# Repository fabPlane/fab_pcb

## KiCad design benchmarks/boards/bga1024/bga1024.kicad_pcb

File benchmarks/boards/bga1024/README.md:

# Eight-layer 1,024-net candidate and report-limit control

Original MIT synthetic fixture, seed 6512. Requires native `pcbnew`, `kicad-cli`
10.0.6 and an output directory that does not exist:

```sh
/usr/bin/python3 -O benchmarks/boards/bga1024/generate.py /tmp/bga1024-new --seed 6512
bun run typecheck
/usr/bin/python3 -O benchmarks/boards/bga1024/test_generate.py
FAB_ROUTER_MODULE=$HOME/bench/repos/fab_router/src/api.ts bun run test:unit
```

The 90 × 90 mm board has eight signal copper layers, a 32 × 32 BGA at 0.5 mm
pitch with 0.2 mm round pads, and four 4 × 64 destination banks with 0.4 mm pads,
0.8 mm horizontal pitch and 1.5 mm row pitch. Each of 1,024 nets has exactly two
terminals (2,048 pads total); destinations are shuffled by the recorded seed.
Track/clearance are 0.10/0.10 mm; through-via diameter/drill are 0.30/0.10 mm.
The companion project is required. There are no planes, pair constraints,
length groups or external footprint libraries. This is an unrouted candidate;
input admission establishes neither routed feasibility nor relative difficulty.

The generator reloads the board and checks net ownership, copper layers,
effective project rules, no tracks/zones, and a fresh native DRC with zero
geometry violations. It exports DSN with a stable root filename. The board,
project and DSN reproduce byte for byte across output directories.

## Native report limit discovered by this board

Native connectivity reports **1,024 opens**, while the fresh DRC JSON report
contains **499 unconnected findings**. These are distinct observations, both
recorded in `summary.json`. KiCad 10.0.6 caps unconnected and clearance findings
at 499 and most other types at 199 in
[its DRC engine](https://github.com/KiCad/kicad-source-mirror/blob/10.0.6/pcbnew/drc/drc_engine.cpp).
A report at the boundary cannot prove an exact count: 499 observed findings
may represent 499 or more actual opens. The fixture remains a diagnostic candidate.
The generator intentionally admits this known report-limited control; it does
not substitute the report count for native connectivity or publish completion.

The benchmark contribution rejects reports at or above the per-type thresholds
before native quality publication and changes cache identity. It conservatively
rejects exact-boundary reports too. Reports below the thresholds are not thereby
proven complete; ignored checks and checker/dependency policy remain separate.
Production native baseline adoption remains pending. The frozen benchmark is
unchanged.

This public contribution contains only the original board, deterministic generator,
native admission test and measurement evidence outside the frozen suite. It does
not change any production router, native checker, scoring or ranked cache policy.
The report-limit rejection was measured in the separate benchmark harness.

Report admission also requires the expected report schema and board name, a
nonempty checker version, error/warning/exclusion coverage, all finding lists,
empty schematic parity and correctly typed error opens. Missing or inconsistent
evidence cannot support the generator's zero-violation diagnostic. Three paired
controls preserve valid admission3/3 while reducing acceptance of nine malformed
variants27/27 to0/27. The mutations apply to fresh reports, not native boards.

```sh
nice -n 10 taskset -c 0-5 timeout 120 /usr/bin/python3 -O benchmarks/boards/bga1024/test_report.py --measure /tmp/bga1024-admission-controls
```

Use a new output directory. The full evidence and limits are retained under
`docs/pr-assets/agent/bga1024-candidate/`.

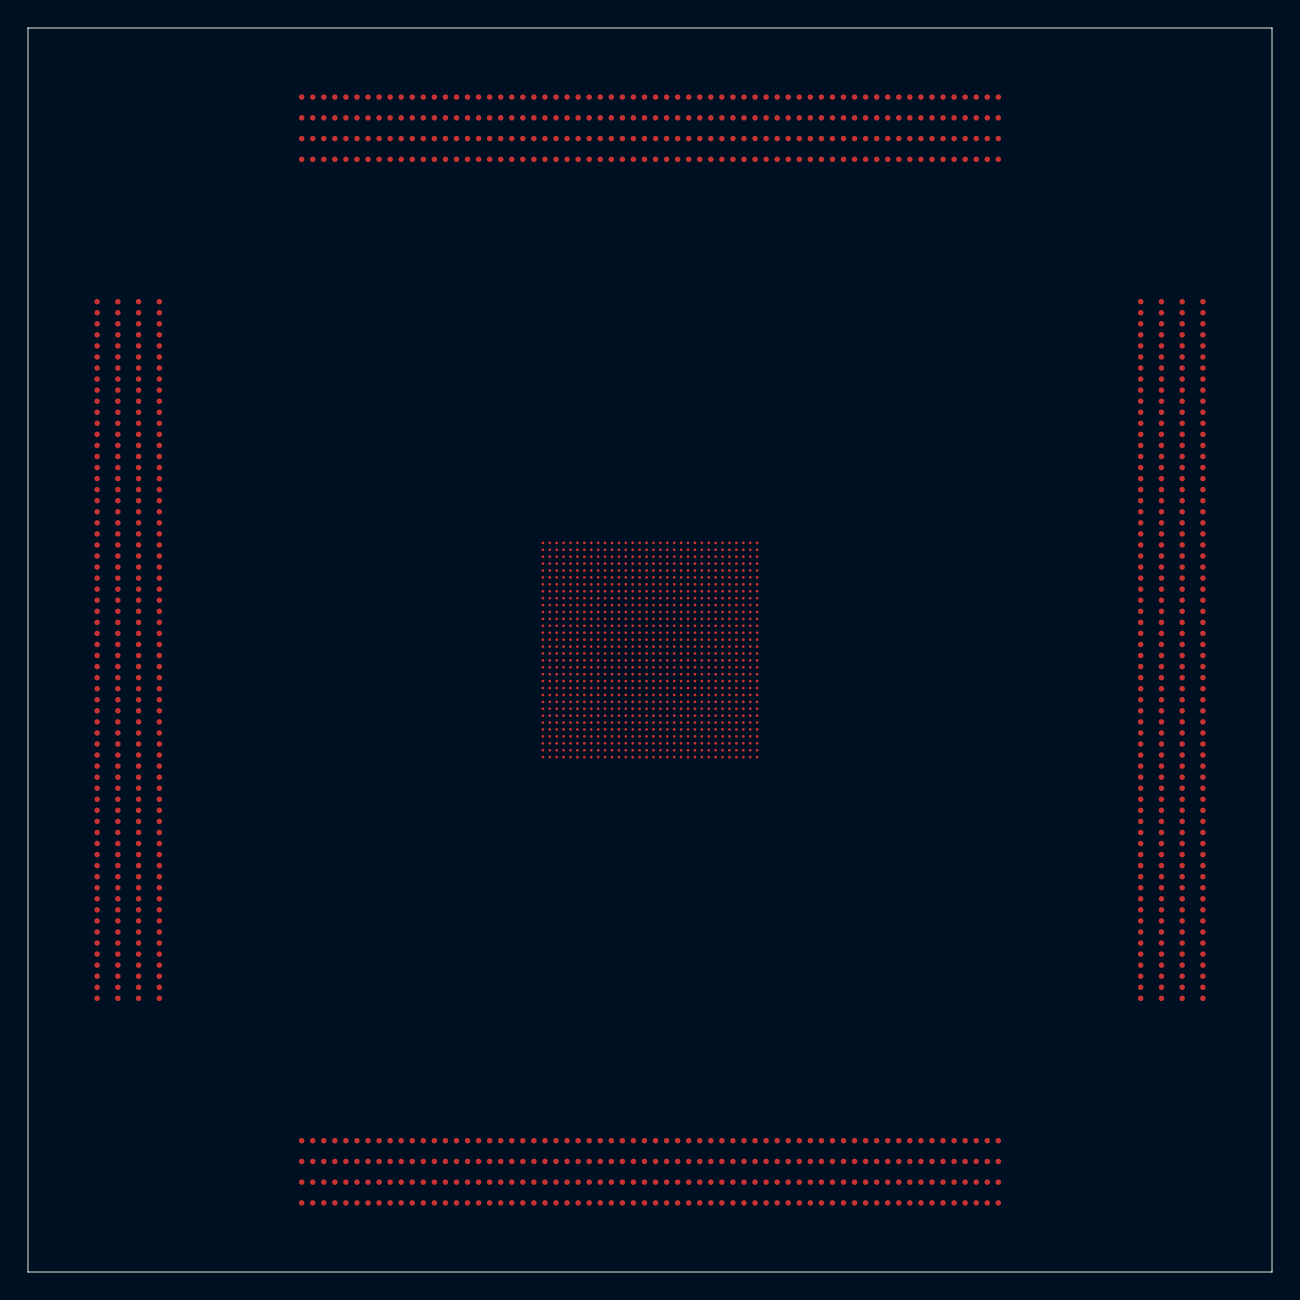
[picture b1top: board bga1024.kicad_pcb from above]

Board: 8 copper layers, 90.0 x 90.0 mm, 1025 parts (0 on the bottom side), 1024 nets, no tracks yet.

Parts:
J1, J2, J3, J4, J5, J6, J7, J8, J9, J10, J11, J12, J13, J14, J15, J16, J17, J18, J19, J20, J21, J22, J23, J24, J25, J26, J27, J28, J29, J30, J31, J32, J33, J34, J35, J36, J37, J38, J39, J40, J41, J42, J43, J44, J45, J46, J47, J48, J49, J50, J51, J52, J53, J54, J55, J56, J57, J58, J59, J60, J61, J62, J63, J64, J65, J66, J67, J68, J69, J70, J71, J72, J73, J74, J75, J76, J77, J78, J79, J80, J81, J82, J83, J84, J85, J86, J87, J88, J89, J90, J91, J92, J93, J94, J95, J96, J97, J98, J99, J100, J101, J102, J103, J104, J105, J106, J107, J108, J109, J110, J111, J112, J113, J114, J115, J116, J117, J118, J119, J120, J121, J122, J123, J124, J125, J126, J127, J128, J129, J130, J131, J132, J133, J134, J135, J136, J137, J138, J139, J140, J141, J142, J143, J144, J145, J146, J147, J148, J149, J150, J151, J152, J153, J154, J155, J156, J157, J158, J159, J160, J161, J162, J163, J164, J165, J166, J167, J168, J169, J170, J171, J172, J173, J174, J175, J176, J177, J178, J179, J180, J181, J182, J183, J184, J185, J186, J187, J188, J189, J190, J191, J192, J193, J194, J195, J196, J197, J198, J199, J200, J201, J202, J203, J204, J205, J206, J207, J208, J209, J210, J211, J212, J213, J214, J215, J216, J217, J218, J219, J220, J221, J222, J223, J224, J225, J226, J227, J228, J229, J230, J231, J232, J233, J234, J235, J236, J237, J238, J239, J240, J241, J242, J243, J244, J245, J246, J247, J248, J249, J250, J251, J252, J253, J254, J255, J256, J257, J258, J259, J260, J261, J262, J263, J264, J265, J266, J267, J268, J269, J270, J271, J272, J273, J274, J275, J276, J277, J278, J279, J280, J281, J282, J283, J284, J285, J286, J287, J288, J289, J290, J291, J292, J293, J294, J295, J296, J297, J298, J299, J300, J301, J302, J303, J304, J305, J306, J307, J308, J309, J310, J311, J312, J313, J314, J315, J316, J317, J318, J319, J320, J321, J322, J323, J324, J325, J326, J327, J328, J329, J330, J331, J332, J333, J334, J335, J336, J337, J338, J339, J340, J341, J342, J343, J344, J345, J346, J347, J348, J349, J350, J351, J352, J353, J354, J355, J356, J357, J358, J359, J360, J361, J362, J363, J364, J365, J366, J367, J368, J369, J370, J371, J372, J373, J374, J375, J376, J377, J378, J379, J380, J381, J382, J383, J384, J385, J386, J387, J388, J389, J390, J391, J392, J393, J394, J395, J396, J397, J398, J399, J400, J401, J402, J403, J404, J405, J406, J407, J408, J409, J410, J411, J412, J413, J414, J415, J416, J417, J418, J419, J420, J421, J422, J423, J424, J425, J426, J427, J428, J429, J430, J431, J432, J433, J434, J435, J436, J437, J438, J439, J440, J441, J442, J443, J444, J445, J446, J447, J448, J449, J450, J451, J452, J453, J454, J455, J456, J457, J458, J459, J460, J461, J462, J463, J464, J465, J466, J467, J468, J469, J470, J471, J472, J473, J474, J475, J476, J477, J478, J479, J480, J481, J482, J483, J484, J485, J486, J487, J488, J489, J490, J491, J492, J493, J494, J495, J496, J497, J498, J499, J500, J501, J502, J503, J504, J505, J506, J507, J508, J509, J510, J511, J512, J513, J514, J515, J516, J517, J518, J519, J520, J521, J522, J523, J524, J525, J526, J527, J528, J529, J530, J531, J532, J533, J534, J535, J536, J537, J538, J539, J540, J541, J542, J543, J544, J545, J546, J547, J548, J549, J550, J551, J552, J553, J554, J555, J556, J557, J558, J559, J560, J561, J562, J563, J564, J565, J566, J567, J568, J569, J570, J571, J572, J573, J574, J575, J576, J577, J578, J579, J580, J581, J582, J583, J584, J585, J586, J587, J588, J589, J590, J591, J592, J593, J594, J595, J596, J597, J598, J599, J600, J601, J602, J603, J604, J605, J606, J607, J608, J609, J610, J611, J612, J613, J614, J615, J616, J617, J618, J619, J620, J621, J622, J623, J624, J625, J626, J627, J628, J629, J630, J631, J632, J633, J634, J635, J636, J637, J638, J639, J640, J641, J642, J643, J644, J645, J646, J647, J648, J649, J650, J651, J652, J653, J654, J655, J656, J657, J658, J659, J660, J661, J662, J663, J664, J665, J666, J667, J668, J669, J670, J671, J672, J673, J674, J675, J676, J677, J678, J679, J680, J681, J682, J683, J684, J685, J686, J687, J688, J689, J690, J691, J692, J693, J694, J695, J696, J697, J698, J699, J700, J701, J702, J703, J704, J705, J706, J707, J708, J709, J710, J711, J712, J713, J714, J715, J716, J717, J718, J719, J720, J721, J722, J723, J724, J725, J726, J727, J728, J729, J730, J731, J732, J733, J734, J735, J736, J737, J738, J739, J740, J741, J742, J743, J744, J745, J746, J747, J748, J749, J750, J751, J752, J753, J754, J755, J756, J757, J758, J759, J760, J761, J762, J763, J764, J765, J766, J767, J768, J769, J770, J771, J772, J773, J774, J775, J776, J777, J778, J779, J780, J781, J782, J783, J784, J785, J786, J787, J788, J789, J790, J791, J792, J793, J794, J795, J796, J797, J798, J799, J800, J801, J802, J803, J804, J805, J806, J807, J808, J809, J810, J811, J812, J813, J814, J815, J816, J817, J818, J819, J820, J821, J822, J823, J824, J825, J826, J827, J828, J829, J830, J831, J832, J833, J834, J835, J836, J837, J838, J839, J840, J841, J842, J843, J844, J845, J846, J847, J848, J849, J850, J851, J852, J853, J854, J855, J856, J857, J858, J859, J860, J861, J862, J863, J864, J865, J866, J867, J868, J869, J870, J871, J872, J873, J874, J875, J876, J877, J878, J879, J880, J881, J882, J883, J884, J885, J886, J887, J888, J889, J890, J891, J892, J893, J894, J895, J896, J897, J898, J899, J900, J901, J902, J903, J904, J905, J906, J907, J908, J909, J910, J911, J912, J913, J914, J915, J916, J917, J918, J919, J920, J921, J922, J923, J924, J925, J926, J927, J928, J929, J930, J931, J932, J933, J934, J935, J936, J937, J938, J939, J940, J941, J942, J943, J944, J945, J946, J947, J948, J949, J950, J951, J952, J953, J954, J955, J956, J957, J958, J959, J960, J961, J962, J963, J964, J965, J966, J967, J968, J969, J970, J971, J972, J973, J974, J975, J976, J977, J978, J979, J980, J981, J982, J983, J984, J985, J986, J987, J988, J989, J990, J991, J992, J993, J994, J995, J996, J997, J998, J999, J1000, J1001, J1002, J1003, J1004, J1005, J1006, J1007, J1008, J1009, J1010, J1011, J1012, J1013, J1014, J1015, J1016, J1017, J1018, J1019, J1020, J1021, J1022, J1023, J1024: escape
U1: escape

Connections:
N1: J358.1, U1.1
N2: J174.2, U1.2
N3: J613.3, U1.3
N4: J73.4, U1.4
N5: J63.5, U1.5
N6: J190.6, U1.6
N7: J628.7, U1.7
N8: J419.8, U1.8
N9: J303.9, U1.9
N10: J916.10, U1.10
N11: J950.11, U1.11
N12: J748.12, U1.12
N13: J988.13, U1.13
N14: J910.14, U1.14
N15: J129.15, U1.15
N16: J452.16, U1.16
N17: J112.17, U1.17
N18: J65.18, U1.18
N19: J379.19, U1.19
N20: J351.20, U1.20
N21: J818.21, U1.21
N22: J10.22, U1.22
N23: J605.23, U1.23
N24: J975.24, U1.24
N25: J929.25, U1.25
N26: J697.26, U1.26
N27: J151.27, U1.27
N28: J108.28, U1.28
N29: J467.29, U1.29
N30: J881.30, U1.30
N31: J1017.31, U1.31
N32: J602.32, U1.32
N33: J445.33, U1.33
N34: J212.34, U1.34
N35: J489.35, U1.35
N36: J476.36, U1.36
N37: J655.37, U1.37
N38: J618.38, U1.38
N39: J856.39, U1.39
N40: J32.40, U1.40
N41: J69.41, U1.41
N42: J763.42, U1.42
N43: J198.43, U1.43
N44: J940.44, U1.44
N45: J255.45, U1.45
N46: J302.46, U1.46
N47: J273.47, U1.47
N48: J540.48, U1.48
N49: J196.49, U1.49
N50: J229.50, U1.50
N51: J576.51, U1.51
N52: J819.52, U1.52
N53: J966.53, U1.53
N54: J4.54, U1.54
N55: J70.55, U1.55
N56: J524.56, U1.56
N57: J363.57, U1.57
N58: J672.58, U1.58
N59: J858.59, U1.59
N60: J963.60, U1.60
N61: J987.61, U1.61
N62: J410.62, U1.62
N63: J327.63, U1.63
N64: J638.64, U1.64
N65: J121.65, U1.65
N66: J991.66, U1.66
N67: J415.67, U1.67
N68: J864.68, U1.68
N69: J435.69, U1.69
N70: J593.70, U1.70
N71: J236.71, U1.71
N72: J660.72, U1.72
N73: J825.73, U1.73
N74: J683.74, U1.74
N75: J74.75, U1.75
N76: J465.76, U1.76
N77: J253.77, U1.77
N78: J38.78, U1.78
N79: J943.79, U1.79
N80: J741.80, U1.80
N81: J501.81, U1.81
N82: J475.82, U1.82
N83: J53.83, U1.83
N84: J592.84, U1.84
N85: J578.85, U1.85
N86: J885.86, U1.86
N87: J869.87, U1.87
N88: J999.88, U1.88
N89: J932.89, U1.89
N90: J295.90, U1.90
N91: J842.91, U1.91
N92: J539.92, U1.92
N93: J333.93, U1.93
N94: J360.94, U1.94
N95: J876.95, U1.95
N96: J348.96, U1.96
N97: J50.97, U1.97
N98: J454.98, U1.98
N99: J846.99, U1.99
N100: J119.100, U1.100
N101: J231.101, U1.101
N102: J67.102, U1.102
N103: J706.103, U1.103
N104: J297.104, U1.104
N105: J554.105, U1.105
N106: J611.106, U1.106
N107: J380.107, U1.107
N108: J541.108, U1.108
N109: J791.109, U1.109
N110: J972.110, U1.110
N111: J39.111, U1.111
N112: J998.112, U1.112
N113: J582.113, U1.113
N114: J753.114, U1.114
N115: J786.115, U1.115
N116: J1016.116, U1.116
N117: J596.117, U1.117
N118: J673.118, U1.118
N119: J532.119, U1.119
N120: J982.120, U1.120
N121: J788.121, U1.121
N122: J874.122, U1.122
N123: J90.123, U1.123
N124: J100.124, U1.124
N125: J948.125, U1.125
N126: J598.126, U1.126
N127: J790.127, U1.127
N128: J136.128, U1.128
N129: J187.129, U1.129
N130: J990.130, U1.130
N131: J644.131, U1.131
N132: J424.132, U1.132
N133: J733.133, U1.133
N134: J77.134, U1.134
N135: J94.135, U1.135
N136: J433.136, U1.136
N137: J848.137, U1.137
N138: J634.138, U1.138
N139: J322.139, U1.139
N140: J1004.140, U1.140
N141: J696.141, U1.141
N142: J588.142, U1.142
N143: J191.143, U1.143
N144: J533.144, U1.144
N145: J543.145, U1.145
N146: J438.146, U1.146
N147: J931.147, U1.147
N148: J239.148, U1.148
N149: J35.149, U1.149
N150: J140.150, U1.150
N151: J870.151, U1.151
N152: J758.152, U1.152
N153: J716.153, U1.153
N154: J1020.154, U1.154
N155: J14.155, U1.155
N156: J835.156, U1.156
N157: J530.157, U1.157
N158: J714.158, U1.158
N159: J985.159, U1.159
N160: J555.160, U1.160
N161: J252.161, U1.161
N162: J793.162, U1.162
N163: J528.163, U1.163
N164: J902.164, U1.164
N165: J738.165, U1.165
N166: J556.166, U1.166
N167: J12.167, U1.167
N168: J369.168, U1.168
N169: J335.169, U1.169
N170: J723.170, U1.170
N171: J690.171, U1.171
N172: J359.172, U1.172
N173: J933.173, U1.173
N174: J305.174, U1.174
N175: J138.175, U1.175
N176: J91.176, U1.176
N177: J175.177, U1.177
N178: J907.178, U1.178
N179: J959.179, U1.179
N180: J549.180, U1.180
N181: J347.181, U1.181
N182: J650.182, U1.182
N183: J310.183, U1.183
N184: J980.184, U1.184
N185: J337.185, U1.185
N186: J219.186, U1.186
N187: J324.187, U1.187
N188: J830.188, U1.188
N189: J765.189, U1.189
N190: J389.190, U1.190
N191: J158.191, U1.191
N192: J234.192, U1.192
N193: J957.193, U1.193
N194: J183.194, U1.194
N195: J155.195, U1.195
N196: J71.196, U1.196
N197: J340.197, U1.197
N198: J285.198, U1.198
N199: J904.199, U1.199
N200: J361.200, U1.200
N201: J671.201, U1.201
N202: J574.202, U1.202
N203: J425.203, U1.203
N204: J715.204, U1.204
N205: J905.205, U1.205
N206: J882.206, U1.206
N207: J72.207, U1.207
N208: J332.208, U1.208
N209: J865.209, U1.209
N210: J908.210, U1.210
N211: J46.211, U1.211
N212: J831.212, U1.212
N213: J325.213, U1.213
N214: J166.214, U1.214
N215: J274.215, U1.215
N216: J407.216, U1.216
N217: J152.217, U1.217
N218: J98.218, U1.218
N219: J544.219, U1.219
N220: J186.220, U1.220
N221: J371.221, U1.221
N222: J460.222, U1.222
N223: J464.223, U1.223
N224: J709.224, U1.224
N225: J339.225, U1.225
N226: J1008.226, U1.226
N227: J62.227, U1.227
N228: J401.228, U1.228
N229: J208.229, U1.229
N230: J180.230, U1.230
N231: J214.231, U1.231
N232: J37.232, U1.232
N233: J996.233, U1.233
N234: J757.234, U1.234
N235: J523.235, U1.235
N236: J779.236, U1.236
N237: J260.237, U1.237
N238: J406.238, U1.238
N239: J935.239, U1.239
N240: J522.240, U1.240
N241: J545.241, U1.241
N242: J286.242, U1.242
N243: J659.243, U1.243
N244: J428.244, U1.244
N245: J58.245, U1.245
N246: J851.246, U1.246
N247: J111.247, U1.247
N248: J936.248, U1.248
N249: J85.249, U1.249
N250: J572.250, U1.250
N251: J761.251, U1.251
N252: J575.252, U1.252
N253: J877.253, U1.253
N254: J562.254, U1.254
N255: J47.255, U1.255
N256: J416.256, U1.256
N257: J206.257, U1.257
N258: J408.258, U1.258
N259: J784.259, U1.259
N260: J150.260, U1.260
N261: J623.261, U1.261
N262: J665.262, U1.262
N263: J711.263, U1.263
N264: J685.264, U1.264
N265: J747.265, U1.265
N266: J43.266, U1.266
N267: J159.267, U1.267
N268: J168.268, U1.268
N269: J639.269, U1.269
N270: J177.270, U1.270
N271: J455.271, U1.271
N272: J233.272, U1.272
N273: J680.273, U1.273
N274: J1009.274, U1.274
N275: J703.275, U1.275
N276: J726.276, U1.276
N277: J749.277, U1.277
N278: J24.278, U1.278
N279: J147.279, U1.279
N280: J204.280, U1.280
N281: J750.281, U1.281
N282: J759.282, U1.282
N283: J355.283, U1.283
N284: J531.284, U1.284
N285: J99.285, U1.285
N286: J1022.286, U1.286
N287: J293.287, U1.287
N288: J281.288, U1.288
N289: J478.289, U1.289
N290: J6.290, U1.290
N291: J441.291, U1.291
N292: J131.292, U1.292
N293: J806.293, U1.293
N294: J319.294, U1.294
N295: J1001.295, U1.295
N296: J713.296, U1.296
N297: J157.297, U1.297
N298: J828.298, U1.298
N299: J341.299, U1.299
N300: J372.300, U1.300
N301: J974.301, U1.301
N302: J511.302, U1.302
N303: J61.303, U1.303
N304: J668.304, U1.304
N305: J27.305, U1.305
N306: J64.306, U1.306
N307: J25.307, U1.307
N308: J20.308, U1.308
N309: J649.309, U1.309
N310: J632.310, U1.310
N311: J95.311, U1.311
N312: J550.312, U1.312
N313: J210.313, U1.313
N314: J947.314, U1.314
N315: J960.315, U1.315
N316: J508.316, U1.316
N317: J440.317, U1.317
N318: J647.318, U1.318
N319: J859.319, U1.319
N320: J813.320, U1.320
N321: J658.321, U1.321
N322: J956.322, U1.322
N323: J352.323, U1.323
N324: J493.324, U1.324
N325: J312.325, U1.325
N326: J51.326, U1.326
N327: J279.327, U1.327
N328: J1003.328, U1.328
N329: J586.329, U1.329
N330: J80.330, U1.330
N331: J497.331, U1.331
N332: J227.332, U1.332
N333: J635.333, U1.333
N334: J654.334, U1.334
N335: J857.335, U1.335
N336: J725.336, U1.336
N337: J901.337, U1.337
N338: J992.338, U1.338
N339: J132.339, U1.339
N340: J466.340, U1.340
N341: J667.341, U1.341
N342: J383.342, U1.342
N343: J430.343, U1.343
N344: J938.344, U1.344
N345: J590.345, U1.345
N346: J381.346, U1.346
N347: J704.347, U1.347
N348: J619.348, U1.348
N349: J486.349, U1.349
N350: J200.350, U1.350
N351: J906.351, U1.351
N352: J79.352, U1.352
N353: J814.353, U1.353
N354: J986.354, U1.354
N355: J448.355, U1.355
N356: J648.356, U1.356
N357: J924.357, U1.357
N358: J762.358, U1.358
N359: J59.359, U1.359
N360: J782.360, U1.360
N361: J93.361, U1.361
N362: J669.362, U1.362
N363: J984.363, U1.363
N364: J269.364, U1.364
N365: J280.365, U1.365
N366: J606.366, U1.366
N367: J900.367, U1.367
N368: J767.368, U1.368
N369: J349.369, U1.369
N370: J785.370, U1.370
N371: J595.371, U1.371
N372: J861.372, U1.372
N373: J583.373, U1.373
N374: J146.374, U1.374
N375: J42.375, U1.375
N376: J1023.376, U1.376
N377: J397.377, U1.377
N378: J559.378, U1.378
N379: J393.379, U1.379
N380: J894.380, U1.380
N381: J783.381, U1.381
N382: J125.382, U1.382
N383: J258.383, U1.383
N384: J429.384, U1.384
N385: J128.385, U1.385
N386: J847.386, U1.386
N387: J215.387, U1.387
N388: J925.388, U1.388
N389: J336.389, U1.389
N390: J500.390, U1.390
N391: J866.391, U1.391
N392: J627.392, U1.392
N393: J873.393, U1.393
N394: J693.394, U1.394
N395: J249.395, U1.395
N396: J496.396, U1.396
N397: J21.397, U1.397
N398: J254.398, U1.398
N399: J326.399, U1.399
N400: J370.400, U1.400
N401: J720.401, U1.401
N402: J211.402, U1.402
N403: J871.403, U1.403
N404: J390.404, U1.404
N405: J422.405, U1.405
N406: J971.406, U1.406
N407: J66.407, U1.407
N408: J220.408, U1.408
N409: J55.409, U1.409
N410: J625.410, U1.410
N411: J778.411, U1.411
N412: J843.412, U1.412
N413: J421.413, U1.413
N414: J291.414, U1.414
N415: J563.415, U1.415
N416: J184.416, U1.416
N417: J617.417, U1.417
N418: J259.418, U1.418
N419: J756.419, U1.419
N420: J232.420, U1.420
N421: J472.421, U1.421
N422: J821.422, U1.422
N423: J624.423, U1.423
N424: J450.424, U1.424
N425: J107.425, U1.425
N426: J197.426, U1.426
N427: J373.427, U1.427
N428: J11.428, U1.428
N429: J506.429, U1.429
N430: J375.430, U1.430
N431: J844.431, U1.431
N432: J535.432, U1.432
N433: J849.433, U1.433
N434: J994.434, U1.434
N435: J491.435, U1.435
N436: J637.436, U1.436
N437: J9.437, U1.437
N438: J178.438, U1.438
N439: J288.439, U1.439
N440: J643.440, U1.440
N441: J542.441, U1.441
N442: J695.442, U1.442
N443: J626.443, U1.443
N444: J742.444, U1.444
N445: J228.445, U1.445
N446: J176.446, U1.446
N447: J616.447, U1.447
N448: J527.448, U1.448
N449: J420.449, U1.449
N450: J773.450, U1.450
N451: J707.451, U1.451
N452: J275.452, U1.452
N453: J414.453, U1.453
N454: J736.454, U1.454
N455: J193.455, U1.455
N456: J705.456, U1.456
N457: J534.457, U1.457
N458: J328.458, U1.458
N459: J942.459, U1.459
N460: J28.460, U1.460
N461: J808.461, U1.461
N462: J250.462, U1.462
N463: J840.463, U1.463
N464: J983.464, U1.464
N465: J892.465, U1.465
N466: J201.466, U1.466
N467: J509.467, U1.467
N468: J36.468, U1.468
N469: J399.469, U1.469
N470: J529.470, U1.470
N471: J453.471, U1.471
N472: J964.472, U1.472
N473: J525.473, U1.473
N474: J954.474, U1.474
N475: J581.475, U1.475
N476: J899.476, U1.476
N477: J679.477, U1.477
N478: J13.478, U1.478
N479: J313.479, U1.479
N480: J518.480, U1.480
N481: J173.481, U1.481
N482: J257.482, U1.482
N483: J447.483, U1.483
N484: J515.484, U1.484
N485: J776.485, U1.485
N486: J97.486, U1.486
N487: J294.487, U1.487
N488: J512.488, U1.488
N489: J630.489, U1.489
N490: J855.490, U1.490
N491: J600.491, U1.491
N492: J833.492, U1.492
N493: J558.493, U1.493
N494: J811.494, U1.494
N495: J872.495, U1.495
N496: J521.496, U1.496
N497: J365.497, U1.497
N498: J296.498, U1.498
N499: J1.499, U1.499
N500: J225.500, U1.500
N501: J677.501, U1.501
N502: J473.502, U1.502
N503: J96.503, U1.503
N504: J678.504, U1.504
N505: J270.505, U1.505
N506: J124.506, U1.506
N507: J737.507, U1.507
N508: J978.508, U1.508
N509: J735.509, U1.509
N510: J795.510, U1.510
N511: J84.511, U1.511
N512: J724.512, U1.512
N513: J426.513, U1.513
N514: J243.514, U1.514
N515: J56.515, U1.515
N516: J34.516, U1.516
N517: J548.517, U1.517
N518: J344.518, U1.518
N519: J394.519, U1.519
N520: J276.520, U1.520
N521: J503.521, U1.521
N522: J391.522, U1.522
N523: J867.523, U1.523
N524: J287.524, U1.524
N525: J652.525, U1.525
N526: J824.526, U1.526
N527: J342.527, U1.527
N528: J87.528, U1.528
N529: J86.529, U1.529
N530: J1013.530, U1.530
N531: J182.531, U1.531
N532: J516.532, U1.532
N533: J955.533, U1.533
N534: J941.534, U1.534
N535: J567.535, U1.535
N536: J78.536, U1.536
N537: J752.537, U1.537
N538: J356.538, U1.538
N539: J1002.539, U1.539
N540: J977.540, U1.540
N541: J264.541, U1.541
N542: J172.542, U1.542
N543: J321.543, U1.543
N544: J194.544, U1.544
N545: J772.545, U1.545
N546: J633.546, U1.546
N547: J45.547, U1.547
N548: J224.548, U1.548
N549: J745.549, U1.549
N550: J88.550, U1.550
N551: J561.551, U1.551
N552: J513.552, U1.552
N553: J83.553, U1.553
N554: J102.554, U1.554
N555: J887.555, U1.555
N556: J495.556, U1.556
N557: J161.557, U1.557
N558: J378.558, U1.558
N559: J22.559, U1.559
N560: J235.560, U1.560
N561: J708.561, U1.561
N562: J396.562, U1.562
N563: J484.563, U1.563
N564: J710.564, U1.564
N565: J485.565, U1.565
N566: J928.566, U1.566
N567: J769.567, U1.567
N568: J171.568, U1.568
N569: J722.569, U1.569
N570: J921.570, U1.570
N571: J385.571, U1.571
N572: J812.572, U1.572
N573: J199.573, U1.573
N574: J437.574, U1.574
N575: J148.575, U1.575
N576: J589.576, U1.576
N577: J743.577, U1.577
N578: J770.578, U1.578
N579: J272.579, U1.579
N580: J412.580, U1.580
N581: J139.581, U1.581
N582: J307.582, U1.582
N583: J934.583, U1.583
N584: J188.584, U1.584
N585: J1015.585, U1.585
N586: J591.586, U1.586
N587: J675.587, U1.587
N588: J621.588, U1.588
N589: J891.589, U1.589
N590: J487.590, U1.590
N591: J939.591, U1.591
N592: J444.592, U1.592
N593: J109.593, U1.593
N594: J571.594, U1.594
N595: J653.595, U1.595
N596: J137.596, U1.596
N597: J919.597, U1.597
N598: J382.598, U1.598
N599: J565.599, U1.599
N600: J969.600, U1.600
N601: J76.601, U1.601
N602: J130.602, U1.602
N603: J944.603, U1.603
N604: J290.604, U1.604
N605: J771.605, U1.605
N606: J101.606, U1.606
N607: J19.607, U1.607
N608: J246.608, U1.608
N609: J41.609, U1.609
N610: J115.610, U1.610
N611: J1014.611, U1.611
N612: J461.612, U1.612
N613: J967.613, U1.613
N614: J712.614, U1.614
N615: J889.615, U1.615
N616: J510.616, U1.616
N617: J456.617, U1.617
N618: J267.618, U1.618
N619: J113.619, U1.619
N620: J505.620, U1.620
N621: J494.621, U1.621
N622: J799.622, U1.622
N623: J699.623, U1.623
N624: J507.624, U1.624
N625: J836.625, U1.625
N626: J149.626, U1.626
N627: J893.627, U1.627
N628: J923.628, U1.628
N629: J517.629, U1.629
N630: J796.630, U1.630
N631: J330.631, U1.631
N632: J357.632, U1.632
N633: J368.633, U1.633
N634: J729.634, U1.634
N635: J16.635, U1.635
N636: J854.636, U1.636
N637: J265.637, U1.637
N638: J449.638, U1.638
N639: J579.639, U1.639
N640: J498.640, U1.640
N641: J245.641, U1.641
N642: J809.642, U1.642
N643: J519.643, U1.643
N644: J681.644, U1.644
N645: J189.645, U1.645
N646: J405.646, U1.646
N647: J860.647, U1.647
N648: J651.648, U1.648
N649: J827.649, U1.649
N650: J629.650, U1.650
N651: J436.651, U1.651
N652: J156.652, U1.652
N653: J57.653, U1.653
N654: J883.654, U1.654
N655: J104.655, U1.655
N656: J661.656, U1.656
N657: J145.657, U1.657
N658: J308.658, U1.658
N659: J803.659, U1.659
N660: J392.660, U1.660
N661: J242.661, U1.661
N662: J961.662, U1.662
N663: J44.663, U1.663
N664: J263.664, U1.664
N665: J283.665, U1.665
N666: J331.666, U1.666
N667: J880.667, U1.667
N668: J734.668, U1.668
N669: J134.669, U1.669
N670: J133.670, U1.670
N671: J244.671, U1.671
N672: J614.672, U1.672
N673: J850.673, U1.673
N674: J760.674, U1.674
N675: J937.675, U1.675
N676: J40.676, U1.676
N677: J277.677, U1.677
N678: J732.678, U1.678
N679: J367.679, U1.679
N680: J30.680, U1.680
N681: J829.681, U1.681
N682: J431.682, U1.682
N683: J483.683, U1.683
N684: J468.684, U1.684
N685: J388.685, U1.685
N686: J284.686, U1.686
N687: J481.687, U1.687
N688: J913.688, U1.688
N689: J135.689, U1.689
N690: J213.690, U1.690
N691: J797.691, U1.691
N692: J230.692, U1.692
N693: J794.693, U1.693
N694: J427.694, U1.694
N695: J268.695, U1.695
N696: J845.696, U1.696
N697: J792.697, U1.697
N698: J164.698, U1.698
N699: J800.699, U1.699
N700: J413.700, U1.700
N701: J181.701, U1.701
N702: J687.702, U1.702
N703: J930.703, U1.703
N704: J514.704, U1.704
N705: J48.705, U1.705
N706: J768.706, U1.706
N707: J684.707, U1.707
N708: J689.708, U1.708
N709: J546.709, U1.709
N710: J366.710, U1.710
N711: J442.711, U1.711
N712: J81.712, U1.712
N713: J398.713, U1.713
N714: J642.714, U1.714
N715: J569.715, U1.715
N716: J346.716, U1.716
N717: J820.717, U1.717
N718: J570.718, U1.718
N719: J764.719, U1.719
N720: J141.720, U1.720
N721: J353.721, U1.721
N722: J477.722, U1.722
N723: J17.723, U1.723
N724: J167.724, U1.724
N725: J853.725, U1.725
N726: J377.726, U1.726
N727: J728.727, U1.727
N728: J411.728, U1.728
N729: J888.729, U1.729
N730: J462.730, U1.730
N731: J807.731, U1.731
N732: J755.732, U1.732
N733: J338.733, U1.733
N734: J185.734, U1.734
N735: J717.735, U1.735
N736: J374.736, U1.736
N737: J266.737, U1.737
N738: J898.738, U1.738
N739: J60.739, U1.739
N740: J195.740, U1.740
N741: J993.741, U1.741
N742: J641.742, U1.742
N743: J205.743, U1.743
N744: J1007.744, U1.744
N745: J320.745, U1.745
N746: J163.746, U1.746
N747: J587.747, U1.747
N748: J838.748, U1.748
N749: J662.749, U1.749
N750: J970.750, U1.750
N751: J499.751, U1.751
N752: J754.752, U1.752
N753: J207.753, U1.753
N754: J54.754, U1.754
N755: J306.755, U1.755
N756: J922.756, U1.756
N757: J612.757, U1.757
N758: J666.758, U1.758
N759: J989.759, U1.759
N760: J82.760, U1.760
N761: J585.761, U1.761
N762: J7.762, U1.762
N763: J688.763, U1.763
N764: J609.764, U1.764
N765: J560.765, U1.765
N766: J343.766, U1.766
N767: J354.767, U1.767
N768: J1000.768, U1.768
N769: J917.769, U1.769
N770: J826.770, U1.770
N771: J404.771, U1.771
N772: J604.772, U1.772
N773: J816.773, U1.773
N774: J223.774, U1.774
N775: J787.775, U1.775
N776: J879.776, U1.776
N777: J918.777, U1.777
N778: J315.778, U1.778
N779: J702.779, U1.779
N780: J409.780, U1.780
N781: J945.781, U1.781
N782: J395.782, U1.782
N783: J886.783, U1.783
N784: J118.784, U1.784
N785: J739.785, U1.785
N786: J841.786, U1.786
N787: J520.787, U1.787
N788: J837.788, U1.788
N789: J240.789, U1.789
N790: J979.790, U1.790
N791: J599.791, U1.791
N792: J434.792, U1.792
N793: J154.793, U1.793
N794: J719.794, U1.794
N795: J117.795, U1.795
N796: J863.796, U1.796
N797: J603.797, U1.797
N798: J731.798, U1.798
N799: J973.799, U1.799
N800: J839.800, U1.800
N801: J890.801, U1.801
N802: J538.802, U1.802
N803: J318.803, U1.803
N804: J298.804, U1.804
N805: J222.805, U1.805
N806: J251.806, U1.806
N807: J953.807, U1.807
N808: J323.808, U1.808
N809: J241.809, U1.809
N810: J282.810, U1.810
N811: J403.811, U1.811
N812: J8.812, U1.812
N813: J301.813, U1.813
N814: J299.814, U1.814
N815: J49.815, U1.815
N816: J271.816, U1.816
N817: J68.817, U1.817
N818: J52.818, U1.818
N819: J502.819, U1.819
N820: J217.820, U1.820
N821: J226.821, U1.821
N822: J620.822, U1.822
N823: J160.823, U1.823
N824: J203.824, U1.824
N825: J387.825, U1.825
N826: J116.826, U1.826
N827: J417.827, U1.827
N828: J317.828, U1.828
N829: J884.829, U1.829
N830: J92.830, U1.830
N831: J868.831, U1.831
N832: J804.832, U1.832
N833: J345.833, U1.833
N834: J573.834, U1.834
N835: J105.835, U1.835
N836: J418.836, U1.836
N837: J674.837, U1.837
N838: J686.838, U1.838
N839: J958.839, U1.839
N840: J316.840, U1.840
N841: J479.841, U1.841
N842: J875.842, U1.842
N843: J75.843, U1.843
N844: J488.844, U1.844
N845: J386.845, U1.845
N846: J636.846, U1.846
N847: J110.847, U1.847
N848: J751.848, U1.848
N849: J292.849, U1.849
N850: J15.850, U1.850
N851: J766.851, U1.851
N852: J89.852, U1.852
N853: J1012.853, U1.853
N854: J536.854, U1.854
N855: J895.855, U1.855
N856: J718.856, U1.856
N857: J469.857, U1.857
N858: J698.858, U1.858
N859: J564.859, U1.859
N860: J557.860, U1.860
N861: J192.861, U1.861
N862: J552.862, U1.862
N863: J384.863, U1.863
N864: J480.864, U1.864
N865: J897.865, U1.865
N866: J1010.866, U1.866
N867: J1005.867, U1.867
N868: J810.868, U1.868
N869: J218.869, U1.869
N870: J31.870, U1.870
N871: J490.871, U1.871
N872: J965.872, U1.872
N873: J664.873, U1.873
N874: J459.874, U1.874
N875: J289.875, U1.875
N876: J1024.876, U1.876
N877: J657.877, U1.877
N878: J962.878, U1.878
N879: J122.879, U1.879
N880: J162.880, U1.880
N881: J364.881, U1.881
N882: J3.882, U1.882
N883: J597.883, U1.883
N884: J103.884, U1.884
N885: J362.885, U1.885
N886: J238.886, U1.886
N887: J911.887, U1.887
N888: J169.888, U1.888
N889: J329.889, U1.889
N890: J997.890, U1.890
N891: J580.891, U1.891
N892: J952.892, U1.892
N893: J334.893, U1.893
N894: J976.894, U1.894
N895: J834.895, U1.895
N896: J566.896, U1.896
N897: J221.897, U1.897
N898: J1006.898, U1.898
N899: J314.899, U1.899
N900: J584.900, U1.900
N901: J143.901, U1.901
N902: J33.902, U1.902
N903: J170.903, U1.903
N904: J601.904, U1.904
N905: J692.905, U1.905
N906: J537.906, U1.906
N907: J927.907, U1.907
N908: J691.908, U1.908
N909: J682.909, U1.909
N910: J903.910, U1.910
N911: J607.911, U1.911
N912: J142.912, U1.912
N913: J951.913, U1.913
N914: J746.914, U1.914
N915: J492.915, U1.915
N916: J615.916, U1.916
N917: J852.917, U1.917
N918: J640.918, U1.918
N919: J18.919, U1.919
N920: J781.920, U1.920
N921: J5.921, U1.921
N922: J721.922, U1.922
N923: J610.923, U1.923
N924: J432.924, U1.924
N925: J153.925, U1.925
N926: J608.926, U1.926
N927: J670.927, U1.927
N928: J402.928, U1.928
N929: J179.929, U1.929
N930: J439.930, U1.930
N931: J553.931, U1.931
N932: J526.932, U1.932
N933: J774.933, U1.933
N934: J946.934, U1.934
N935: J700.935, U1.935
N936: J777.936, U1.936
N937: J1021.937, U1.937
N938: J805.938, U1.938
N939: J463.939, U1.939
N940: J474.940, U1.940
N941: J23.941, U1.941
N942: J981.942, U1.942
N943: J446.943, U1.943
N944: J423.944, U1.944
N945: J832.945, U1.945
N946: J862.946, U1.946
N947: J165.947, U1.947
N948: J780.948, U1.948
N949: J1018.949, U1.949
N950: J568.950, U1.950
N951: J376.951, U1.951
N952: J817.952, U1.952
N953: J912.953, U1.953
N954: J878.954, U1.954
N955: J676.955, U1.955
N956: J443.956, U1.956
N957: J470.957, U1.957
N958: J261.958, U1.958
N959: J237.959, U1.959
N960: J300.960, U1.960
N961: J801.961, U1.961
N962: J256.962, U1.962
N963: J789.963, U1.963
N964: J744.964, U1.964
N965: J646.965, U1.965
N966: J126.966, U1.966
N967: J701.967, U1.967
N968: J694.968, U1.968
N969: J822.969, U1.969
N970: J622.970, U1.970
N971: J262.971, U1.971
N972: J458.972, U1.972
N973: J400.973, U1.973
N974: J949.974, U1.974
N975: J457.975, U1.975
N976: J775.976, U1.976
N977: J26.977, U1.977
N978: J202.978, U1.978
N979: J248.979, U1.979
N980: J209.980, U1.980
N981: J451.981, U1.981
N982: J798.982, U1.982
N983: J123.983, U1.983
N984: J577.984, U1.984
N985: J114.985, U1.985
N986: J915.986, U1.986
N987: J656.987, U1.987
N988: J594.988, U1.988
N989: J504.989, U1.989
N990: J120.990, U1.990
N991: J278.991, U1.991
N992: J896.992, U1.992
N993: J920.993, U1.993
N994: J663.994, U1.994
N995: J309.995, U1.995
N996: J968.996, U1.996
N997: J247.997, U1.997
N998: J216.998, U1.998
N999: J909.999, U1.999
N1000: J645.1000, U1.1000
N1001: J631.1001, U1.1001
N1002: J823.1002, U1.1002
N1003: J740.1003, U1.1003
N1004: J1011.1004, U1.1004
N1005: J914.1005, U1.1005
N1006: J926.1006, U1.1006
N1007: J29.1007, U1.1007
N1008: J106.1008, U1.1008
N1009: J350.1009, U1.1009
N1010: J1019.1010, U1.1010
N1011: J730.1011, U1.1011
N1012: J304.1012, U1.1012
N1013: J144.1013, U1.1013
N1014: J802.1014, U1.1014
N1015: J551.1015, U1.1015
N1016: J471.1016, U1.1016
N1017: J482.1017, U1.1017
N1018: J311.1018, U1.1018
N1019: J995.1019, U1.1019
N1020: J727.1020, U1.1020
N1021: J127.1021, U1.1021
N1022: J815.1022, U1.1022
N1023: J2.1023, U1.1023
N1024: J547.1024, U1.1024
